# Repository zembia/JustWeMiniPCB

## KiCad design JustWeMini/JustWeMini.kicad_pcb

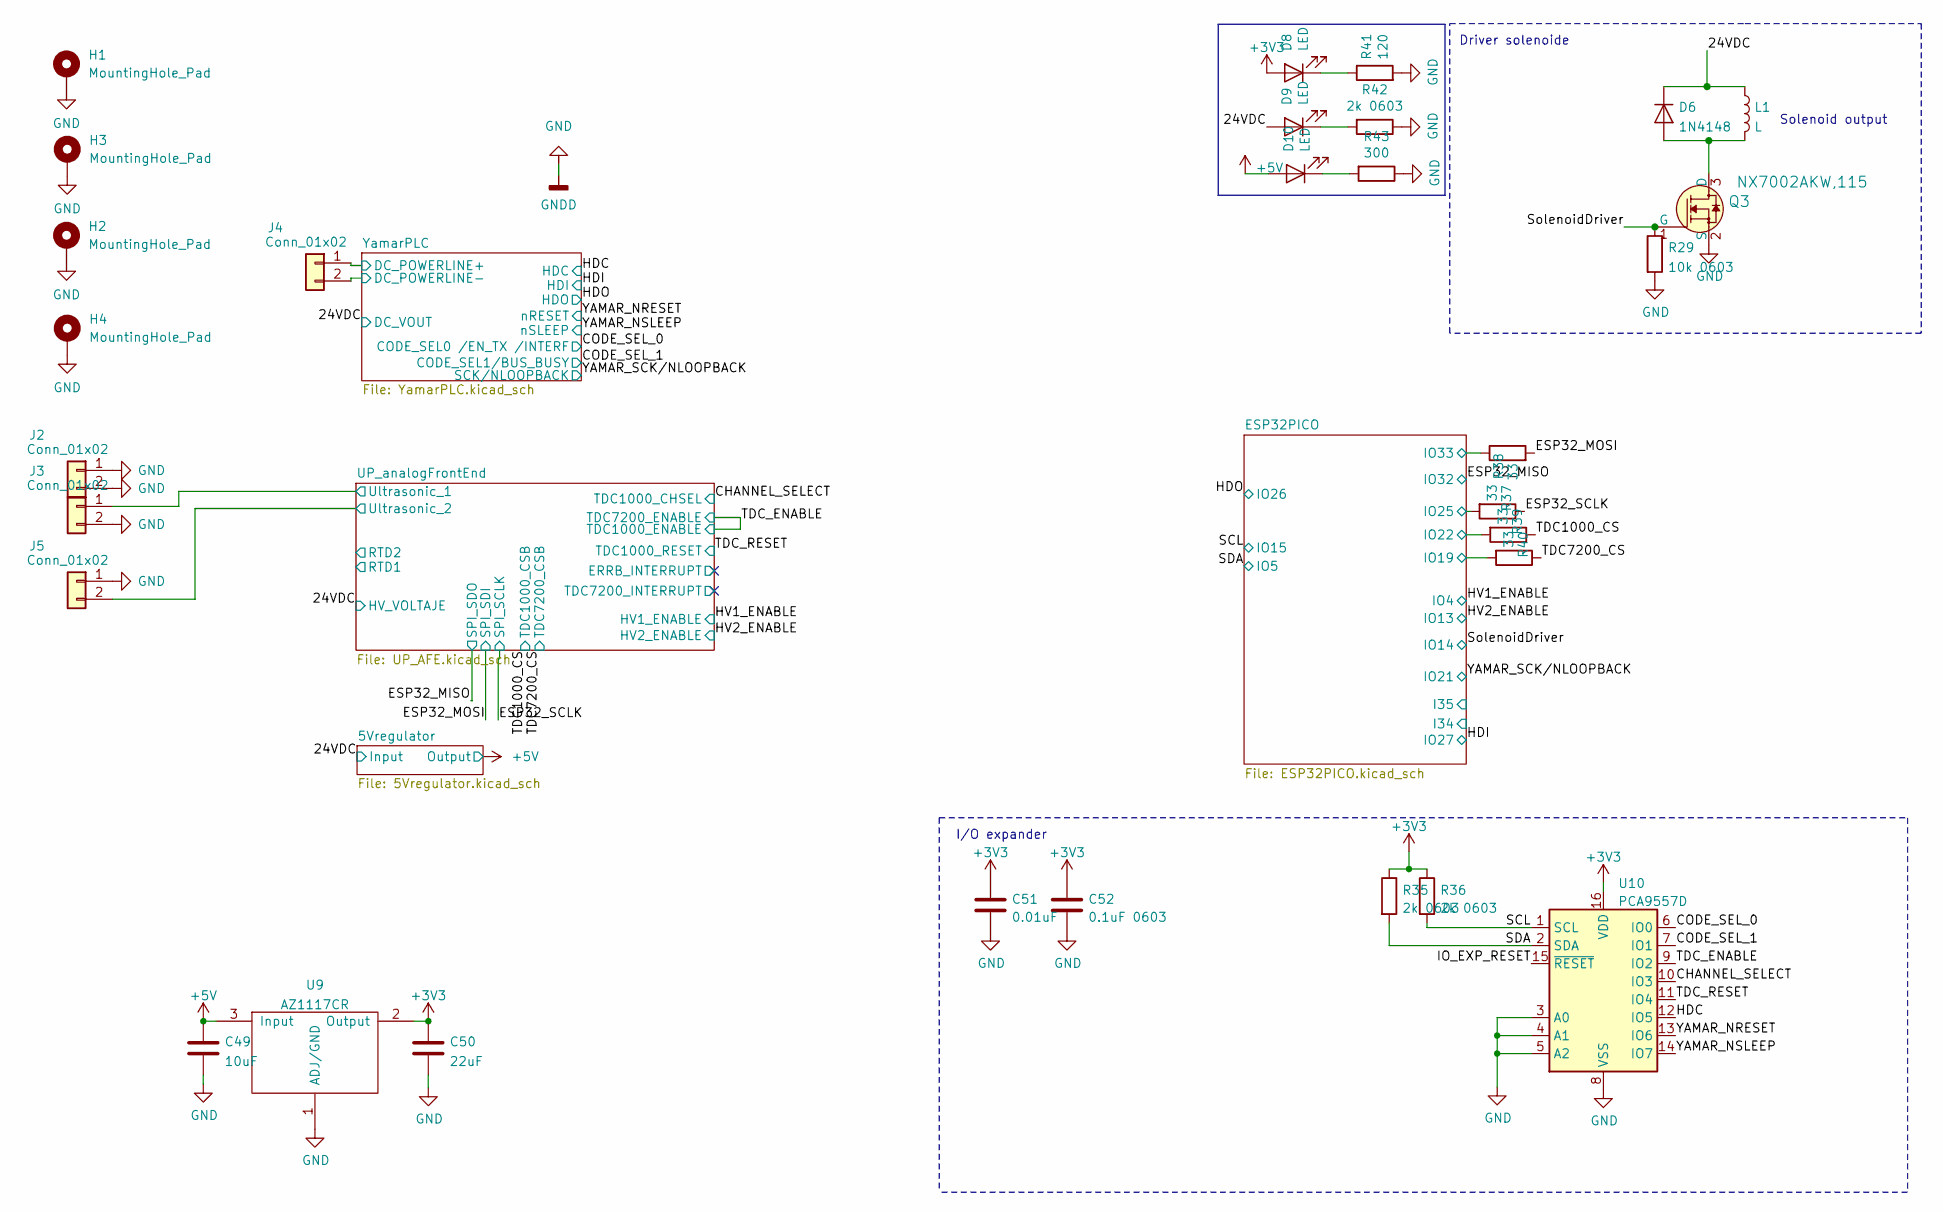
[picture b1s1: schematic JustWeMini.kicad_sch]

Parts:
C49: 10uF; C_0805_2012Metric; MPN GRM21BR6YA106ME43L
C50: 22uF; C_0603_1608Metric; MPN GRM187R61A226ME15D
C51: 0.01uF; C_0402_1005Metric; MPN CC0402JRX7R9BB103
C52: 0.1uF 0603; C_0603_1608Metric; MPN C0603C104K5RAC3121
D6: 1N4148; D_DO-35_SOD27_P7.62mm_Horizontal; MPN 1N4148
D8, D9, D10: LED; LED_0805_2012Metric; MPN SM0805UYC
H1, H2, H3, H4: MountingHole_Pad; MountingHole_3.2mm_M3_Pad_Via
J2, J3, J4, J5: Conn_01x02; CUI_TB007-508-02BE; MPN TB007-508-02BE
L1: L; CUI_TB007-508-02BE; MPN TB007-508-02BE
Q3: -; SOT-323_SC-70; MPN NX7002AKW,115
R29: 10k 0603; R_0603_1608Metric; MPN CR0603-FX-1002ELF
R35, R36, R42: 2k 0603; R_0603_1608Metric; MPN ERJ-PA3F2001V
R37, R38, R39, R40: 33; R_0402_1005Metric; MPN CR0402-FX-33R0GLF
R41: 120; R_0603_1608Metric; MPN CR0603-JW-121ELF
R43: 300; R_0603_1608Metric; MPN RC0603JR-07300RL
U9: AZ1117CR; SOT-89-3; MPN AZ1117CR-3.3TRG1
U10: PCA9557D; SO-16_3.9x9.9mm_P1.27mm; MPN PCA9557D

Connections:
+3V3: C50.1, C51.1, C52.1, D8.2 (A), R35.1, R36.1, U9.2 (Output), U10.16 (VDD); also elsewhere on the board
+5V: C49.1, D10.2 (A), U9.3 (Input); also elsewhere on the board
/24VDC: D6.1 (K), D9.2 (A), L1.1; also elsewhere on the board
/CHANNEL_SELECT: U10.10 (IO3); also elsewhere on the board
/CODE_SEL_0: U10.6 (IO0); also elsewhere on the board
/CODE_SEL_1: U10.7 (IO1); also elsewhere on the board
/ESP32PICO/IO19: R40.2; also elsewhere on the board
/ESP32PICO/IO22: R39.2; also elsewhere on the board
/ESP32PICO/IO25: R37.2; also elsewhere on the board
/ESP32PICO/IO33: R38.1; also elsewhere on the board
/ESP32_MOSI: R38.2; also elsewhere on the board
/ESP32_SCLK: R37.1; also elsewhere on the board
/HDC: U10.12 (IO5); also elsewhere on the board
/IO_EXP_RESET: U10.15 (~RESET)
/SCL: R36.2, U10.1 (SCL); also elsewhere on the board
/SDA: R35.2, U10.2 (SDA); also elsewhere on the board
/SolenoidDriver: Q3.1 (G), R29.1; also elsewhere on the board
/TDC1000_CS: R39.1; also elsewhere on the board
/TDC7200_CS: R40.1; also elsewhere on the board
/TDC_ENABLE: U10.9 (IO2); also elsewhere on the board
/TDC_RESET: U10.11 (IO4); also elsewhere on the board
/UP_analogFrontEnd/Ultrasonic_1: J3.1; also elsewhere on the board
/UP_analogFrontEnd/Ultrasonic_2: J5.2; also elsewhere on the board
/YAMAR_NRESET: U10.13 (IO6); also elsewhere on the board
/YAMAR_NSLEEP: U10.14 (IO7); also elsewhere on the board
/YamarPLC/DC_POWERLINE+: J4.1; also elsewhere on the board
GND: C49.2, C50.2, C51.2, C52.2, H1.1, H2.1, H3.1, H4.1, J2.1, J2.2, J3.2, J4.2, J5.1, Q3.2 (S), R29.2, R41.2, R42.1, R43.1, U9.1 (ADJ/GND), U10.3 (A0), U10.4 (A1), U10.5 (A2), U10.8 (VSS); also elsewhere on the board
unnamed: D6.2 (A), L1.2, Q3.3 (D)
unnamed: D8.1 (K), R41.1
unnamed: D9.1 (K), R42.2
unnamed: D10.1 (K), R43.2

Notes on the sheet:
Driver solenoide
Solenoid output
I/O expander

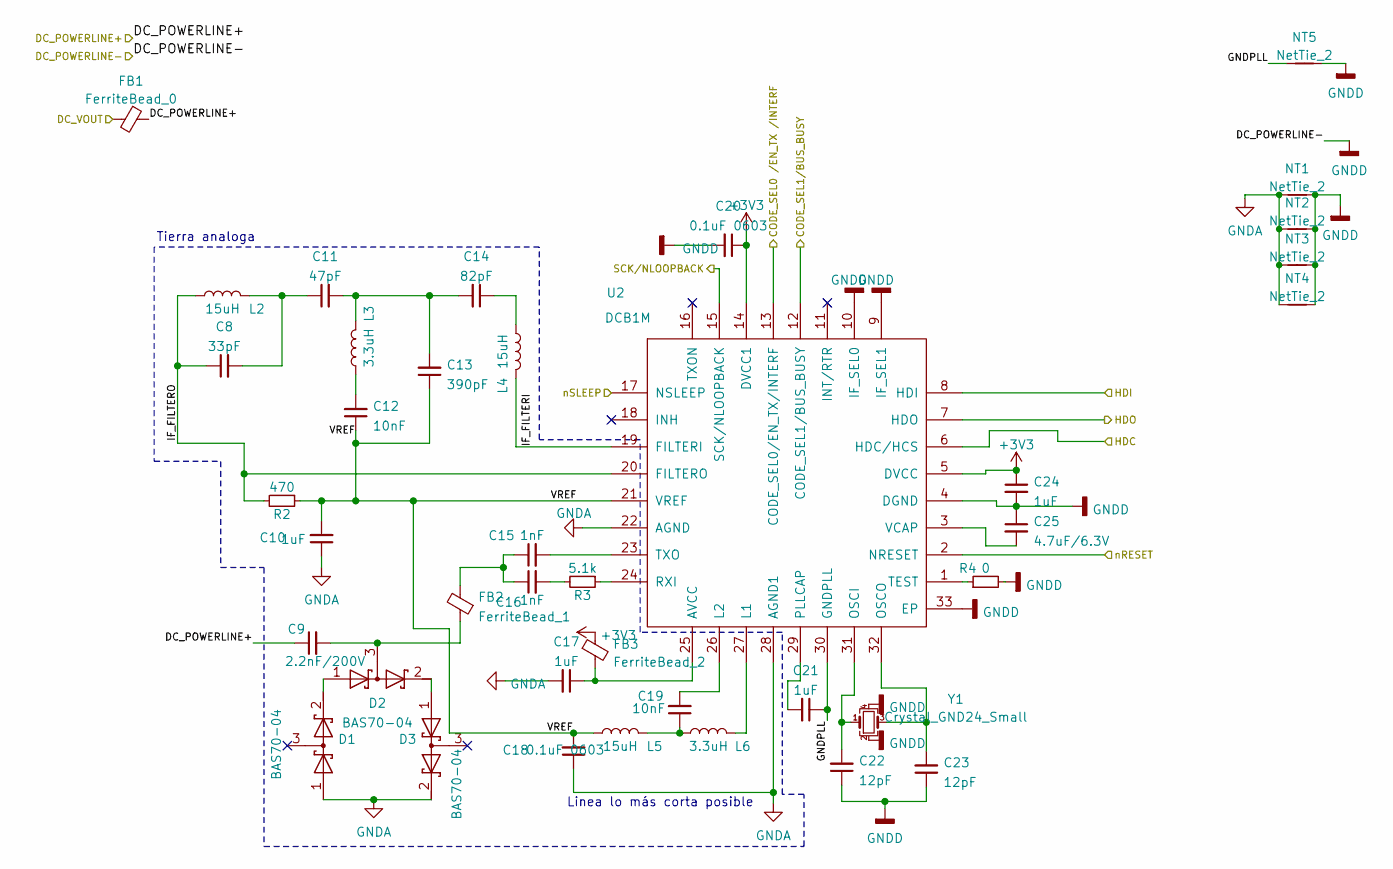
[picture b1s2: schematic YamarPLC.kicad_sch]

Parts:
C8: 33pF; C_0603_1608Metric; MPN 06035A330FAT2A
C9: 2.2nF/200V; C_0603_1608Metric; MPN C0603C222K2RECAUTO
C10, C17, C24: 1uF; C_0805_2012Metric; MPN C2012JB1V105M085AB
C11: 47pF; C_0402_1005Metric; MPN 0402N470J250CT
C12, C19: 10nF; C_0603_1608Metric; MPN VJ0603Y103KXAAC
C13: 390pF; C_0402_1005Metric; MPN 0402N391J250CT
C14: 82pF; C_0603_1608Metric; MPN VJ0603A820JXAAC
C15, C16: 1nF; C_0603_1608Metric; MPN GRM1885C1H102JA01D
C18, C20: 0.1uF 0603; C_0603_1608Metric; MPN C0603C104K5RAC3121
C21: 1uF; C_0603_1608Metric; MPN LMK107B7105KA-T
C22, C23: 12pF; C_0603_1608Metric; MPN VJ0603D120JXPAJ
C25: 4.7uF/6.3V; C_0603_1608Metric; MPN GCJ188C70J475KE02D
D1, D2, D3: BAS70-04; SOT-23; MPN BAS70-04 RFG
FB1: FerriteBead_0; L_Taiyo-Yuden_NR-50xx; MPN NRS5040T220MMGK
FB2: FerriteBead_1; L_0603_1608Metric; MPN-DK MI0603L301R-10
FB3: FerriteBead_2; L_0603_1608Metric; MPN HZ0603A222R-10
L2, L4, L5: 15uH; L_0805_2012Metric; MPN 815-AIML-0805-150K-T
L3, L6: 3.3uH; L_0805_2012Metric; MPN AIML-0805-3R3K-T
NT1, NT2, NT3, NT4, NT5: NetTie_2; NetTie-2_SMD_Pad0.25mm
R2: 470; R_0603_1608Metric; MPN CRGCQ0603F470R
R3: 5.1k; R_0603_1608Metric; MPN CR0603-JW-512ELF
R4: 0; R_0603_1608Metric; MPN CRCW06030000Z0EAHP
U2: DCB1M; QFN-32-1EP_5x5mm_P0.5mm_EP3.3x3.3mm; MPN DCB1M
Y1: Crystal_GND24_Small; Crystal_SMD_2016-4Pin_2.0x1.6mm; MPN ECS-160-12-37B-CTN-TR

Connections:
+3V3: C20.1, C24.1, FB3.1, U2.5 (DVCC), U2.14 (DVCC1); also elsewhere on the board
/24VDC: FB1.2; also elsewhere on the board
/CODE_SEL_0: U2.13 (CODE_SEL0/EN_TX/INTERF); also elsewhere on the board
/CODE_SEL_1: U2.12 (CODE_SEL1/BUS_BUSY); also elsewhere on the board
/HDC: U2.6 (HDC/HCS); also elsewhere on the board
/HDI: U2.8 (HDI); also elsewhere on the board
/HDO: U2.7 (HDO); also elsewhere on the board
/YAMAR_NRESET: U2.2 (NRESET); also elsewhere on the board
/YAMAR_NSLEEP: U2.17 (NSLEEP); also elsewhere on the board
/YAMAR_SCK/NLOOPBACK: U2.15 (SCK/NLOOPBACK); also elsewhere on the board
/YamarPLC/DC_POWERLINE+: C9.1, FB1.1; also elsewhere on the board
/YamarPLC/GNDPLL: C21.1, NT5.1, U2.30 (GNDPLL)
/YamarPLC/IF_FILTERI: L4.1, U2.19 (FILTERI)
/YamarPLC/IF_FILTERO: C8.1, L2.2, R2.2, U2.20 (FILTERO)
/YamarPLC/VREF: C10.2, C12.1, C13.1, C18.2, L5.2, R2.1, U2.21 (VREF)
GND: C20.2, C22.1, C23.1, C24.2, C25.1, NT1.2, NT2.2, NT3.2, NT4.2, NT5.2, R4.2, U2.4 (DGND), U2.9 (IF_SEL1), U2.10 (IF_SEL0), U2.33 (EP), Y1.2, Y1.4; also elsewhere on the board
GNDA: C10.1, C17.2, C18.1, D1.1 (A), D3.2 (K), NT1.1, NT2.1, NT3.1, NT4.1, U2.22 (AGND), U2.28 (AGND1)
unnamed: C9.2, D2.3 (common), FB2.1
unnamed: C8.2, C11.1, L2.1
unnamed: C11.2, C13.2, C14.2, L3.1
unnamed: C12.2, L3.2
unnamed: C14.1, L4.2
unnamed: C15.1, C16.1, FB2.2
unnamed: C15.2, U2.23 (TXO)
unnamed: C16.2, R3.2
unnamed: C17.1, FB3.2, U2.25 (AVCC)
unnamed: C19.1, L5.1, L6.2
unnamed: C19.2, U2.26 (L2)
unnamed: C21.2, U2.29 (PLLCAP)
unnamed: C22.2, U2.31 (OSCI), Y1.1
unnamed: C23.2, U2.32 (OSCO), Y1.3
unnamed: C25.2, U2.3 (VCAP)
unnamed: D1.2 (K), D2.1 (A)
unnamed: D2.2 (K), D3.1 (A)
unnamed: L6.1, U2.27 (L1)
unnamed: R3.1, U2.24 (RXI)
unnamed: R4.1, U2.1 (TEST)

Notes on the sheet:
Linea lo más corta posible
Tierra analoga

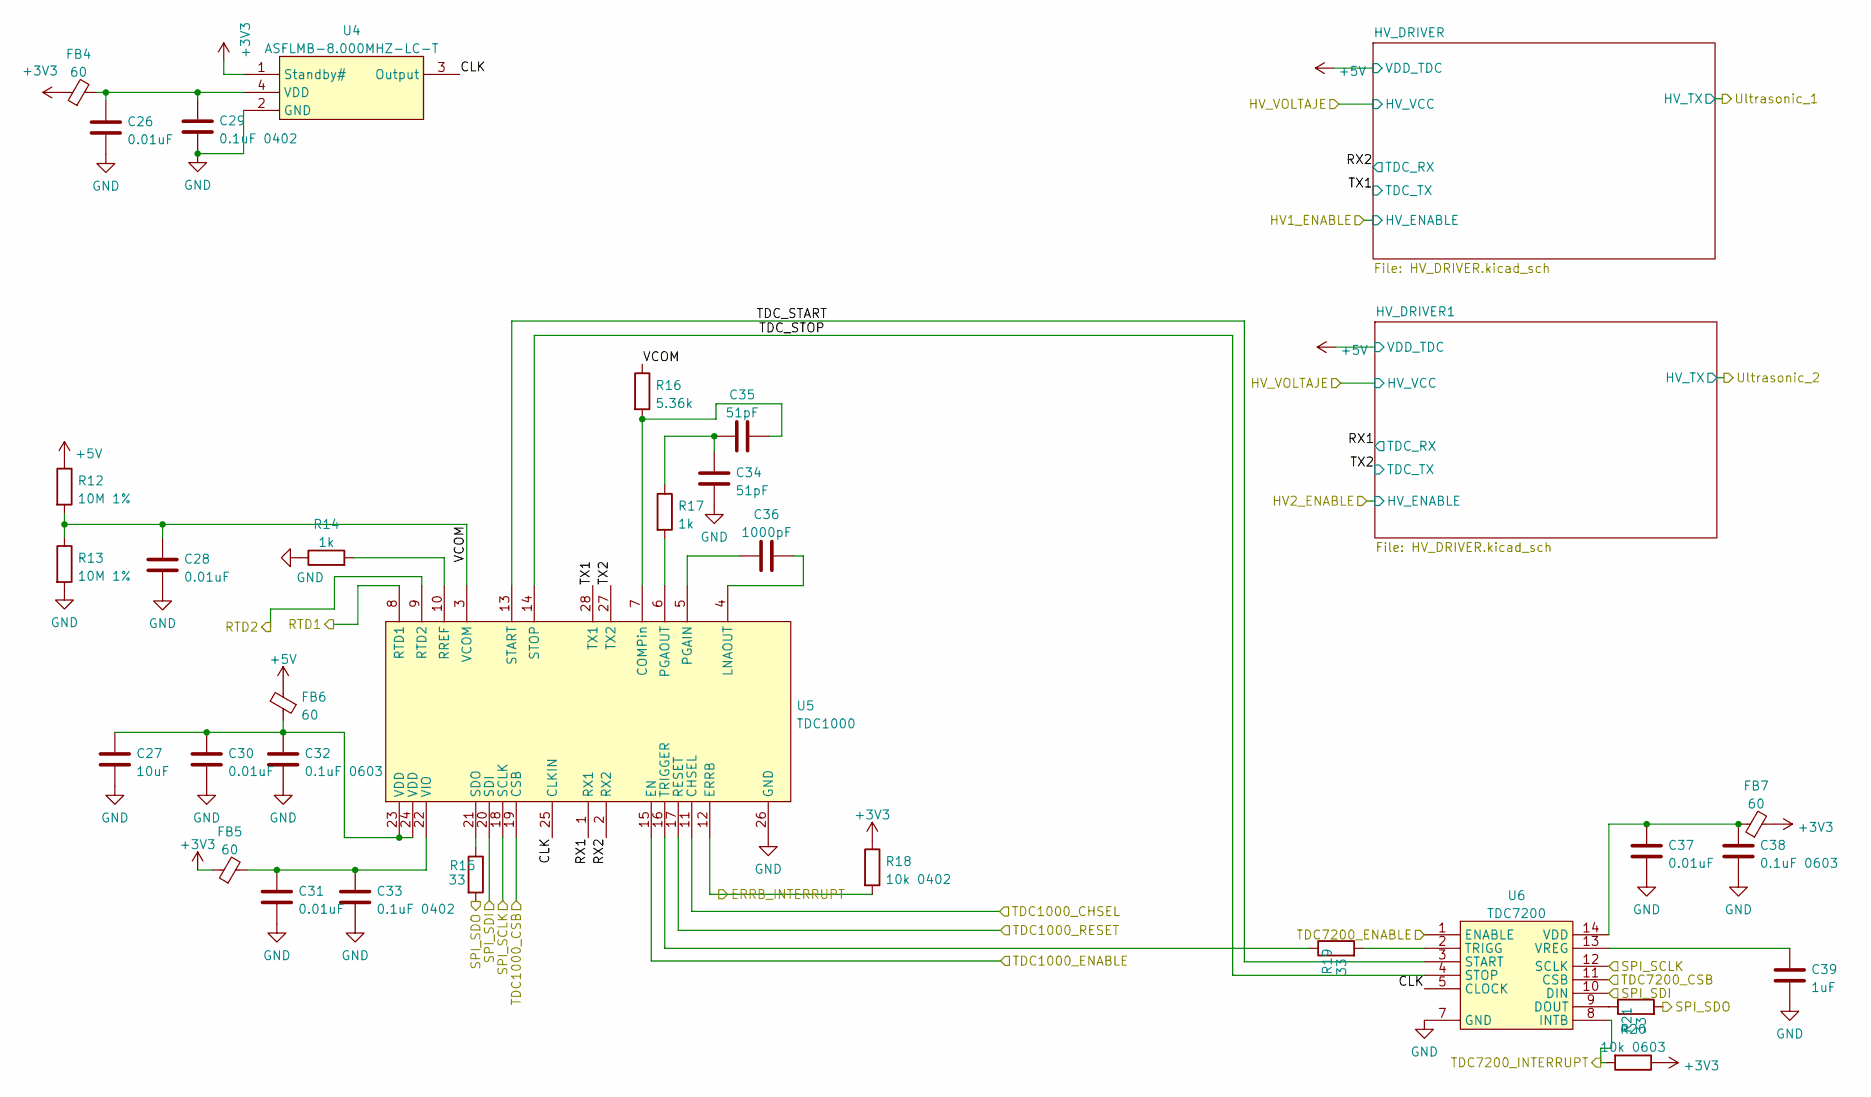
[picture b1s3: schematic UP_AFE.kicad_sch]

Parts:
C26, C28, C30, C31, C37: 0.01uF; C_0402_1005Metric; MPN CC0402JRX7R9BB103
C27: 10uF; C_0805_2012Metric; MPN GRM21BR6YA106ME43L
C29, C33: 0.1uF 0402; C_0402_1005Metric; MPN CL05F104ZO5NNND
C32, C38: 0.1uF 0603; C_0603_1608Metric; MPN C0603C104K5RAC3121
C34, C35: 51pF; C_0402_1005Metric; MPN CC0402JRNPO9BN510
C36: 1000pF; C_0402_1005Metric; MPN 0402B102J500CT
C39: 1uF; C_0805_2012Metric; MPN C2012JB1V105M085AB
FB4, FB5, FB6, FB7: 60; L_0402_1005Metric; MPN ACML-0402HC-600-T
R12, R13: 10M 1%; R_0402_1005Metric; MPN RC0402FR-0710ML
R14, R17: 1k; R_0402_1005Metric; MPN RC0402JR-071KL
R15, R19, R21: 33; R_0402_1005Metric; MPN CR0402-FX-33R0GLF
R16: 5.36k; R_0603_1608Metric; MPN AC0603FR-075K36L
R18: 10k 0402; R_0402_1005Metric; MPN WR04X1002FTL
R20: 10k 0603; R_0603_1608Metric; MPN CR0603-FX-1002ELF
U4: ASFLMB-8.000MHZ-LC-T; ASFLMB; MPN ASFLMB-8.000MHZ-LC-T
U5: TDC1000; TSSOP-28_4.4x9.7mm_P0.65mm; MPN TDC1000PW
U6: TDC7200; TSSOP-14_4.4x5mm_P0.65mm; MPN TDC7200PWR

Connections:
+3V3: FB4.1, FB5.1, FB7.2, R18.1, R20.1, U4.1 (Standby#); also elsewhere on the board
+5V: FB6.2, R12.1; also elsewhere on the board
/CHANNEL_SELECT: U5.11 (CHSEL); also elsewhere on the board
/ESP32_MISO: R15.2, R21.2; also elsewhere on the board
/ESP32_MOSI: U5.20 (SDI), U6.10 (DIN); also elsewhere on the board
/ESP32_SCLK: U5.18 (SCLK), U6.12 (SCLK); also elsewhere on the board
/TDC1000_CS: U5.19 (CSB); also elsewhere on the board
/TDC7200_CS: U6.11 (CSB); also elsewhere on the board
/TDC_ENABLE: U5.15 (EN), U6.1 (ENABLE); also elsewhere on the board
/TDC_RESET: U5.17 (RESET); also elsewhere on the board
/UP_analogFrontEnd/CLK: U4.3 (Output), U5.25 (CLKIN), U6.5 (CLOCK)
/UP_analogFrontEnd/ERRB_INTERRUPT: R18.2, U5.12 (ERRB)
/UP_analogFrontEnd/RTD1: U5.8 (RTD1)
/UP_analogFrontEnd/RTD2: U5.9 (RTD2)
/UP_analogFrontEnd/RX1: U5.1 (RX1); also elsewhere on the board
/UP_analogFrontEnd/RX2: U5.2 (RX2); also elsewhere on the board
/UP_analogFrontEnd/TDC7200_INTERRUPT: R20.2, U6.8 (INTB)
/UP_analogFrontEnd/TDC_START: U5.13 (START), U6.3 (START)
/UP_analogFrontEnd/TDC_STOP: U5.14 (STOP), U6.4 (STOP)
/UP_analogFrontEnd/TX1: U5.28 (TX1); also elsewhere on the board
/UP_analogFrontEnd/TX2: U5.27 (TX2); also elsewhere on the board
/UP_analogFrontEnd/VCOM: C28.1, R12.2, R13.1, R16.1, U5.3 (VCOM)
GND: C26.2, C27.2, C28.2, C29.2, C30.2, C31.2, C32.2, C33.2, C34.1, C37.2, C38.2, C39.2, R13.2, R14.1, U4.2 (GND), U5.26 (GND), U6.7 (GND); also elsewhere on the board
unnamed: C26.1, C29.1, FB4.2, U4.4 (VDD)
unnamed: C27.1, C30.1, C32.1, FB6.1, U5.23 (VDD), U5.24 (VDD)
unnamed: C31.1, C33.1, FB5.2, U5.22 (VIO)
unnamed: C34.2, C35.1, R17.1
unnamed: C35.2, R16.2, U5.7 (COMPin)
unnamed: C36.1, U5.5 (PGAIN)
unnamed: C36.2, U5.4 (LNAOUT)
unnamed: C37.1, C38.1, FB7.1, U6.14 (VDD)
unnamed: C39.1, U6.13 (VREG)
unnamed: R14.2, U5.10 (RREF)
unnamed: R15.1, U5.21 (SDO)
unnamed: R17.2, U5.6 (PGAOUT)
unnamed: R19.1, U5.16 (TRIGGER)
unnamed: R19.2, U6.2 (TRIGG)
unnamed: R21.1, U6.9 (DOUT)

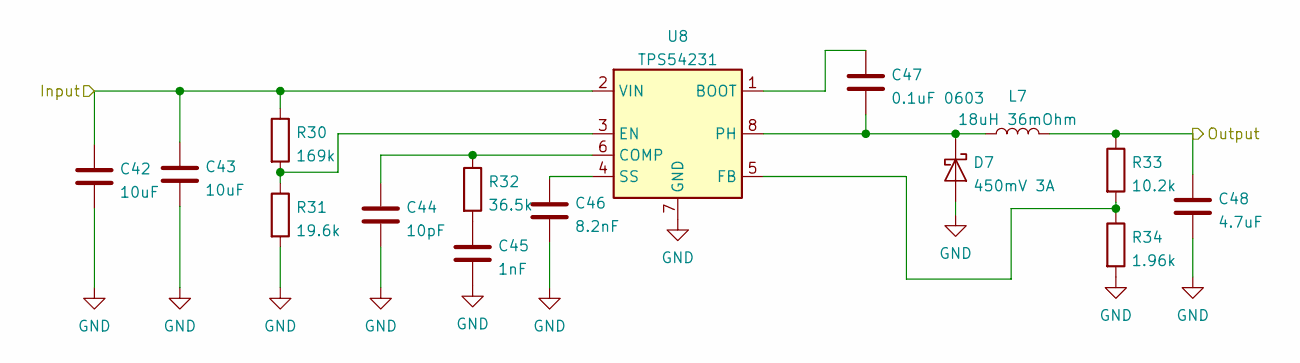
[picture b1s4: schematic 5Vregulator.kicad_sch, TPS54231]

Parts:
C42, C43: 10uF; C_0805_2012Metric; MPN GRM21BR6YA106ME43L
C44: 10pF; C_0603_1608Metric; MPN 06035C100KAT2A
C45: 1nF; C_0603_1608Metric; MPN GRM1885C1H102JA01D
C46: 8.2nF; C_0603_1608Metric; MPN CGA3E2C0G1H822J080AE
C47: 0.1uF 0603; C_0603_1608Metric; MPN C0603C104K5RAC3121
C48: 4.7uF; C_0603_1608Metric; MPN C1608JB1E475M080AC
D7: 450mV 3A; D_SMA; MPN B340A-E3/61T
L7: 18uH 36mOhm; L_Bourns_SRR1260; MPN SRR1280-180M
R30: 169k; R_0603_1608Metric; MPN RC0603FR-07169KL
R31: 19.6k; R_0603_1608Metric; MPN RC0603FR-0719K6L
R32: 36.5k; R_0603_1608Metric; MPN CR0603-FX-3652ELF
R33: 10.2k; R_0603_1608Metric; MPN RC0603FR-1310K2L
R34: 1.96k; R_0603_1608Metric; MPN AC0603FR-071K96L
U8: TPS54231; SOIC-8_3.9x4.9mm_P1.27mm; MPN TPS54231DR

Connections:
+5V: C48.1, L7.2, R33.1; also elsewhere on the board
/24VDC: C42.1, C43.1, R30.1, U8.2 (VIN); also elsewhere on the board
GND: C42.2, C43.2, C44.2, C45.2, C46.2, C48.2, D7.2 (A), R31.2, R34.2, U8.7 (GND); also elsewhere on the board
unnamed: C44.1, R32.1, U8.6 (COMP)
unnamed: C45.1, R32.2
unnamed: C46.1, U8.4 (SS)
unnamed: C47.1, U8.1 (BOOT)
unnamed: C47.2, D7.1 (K), L7.1, U8.8 (PH)
unnamed: R30.2, R31.1, U8.3 (EN)
unnamed: R33.2, R34.1, U8.5 (FB)

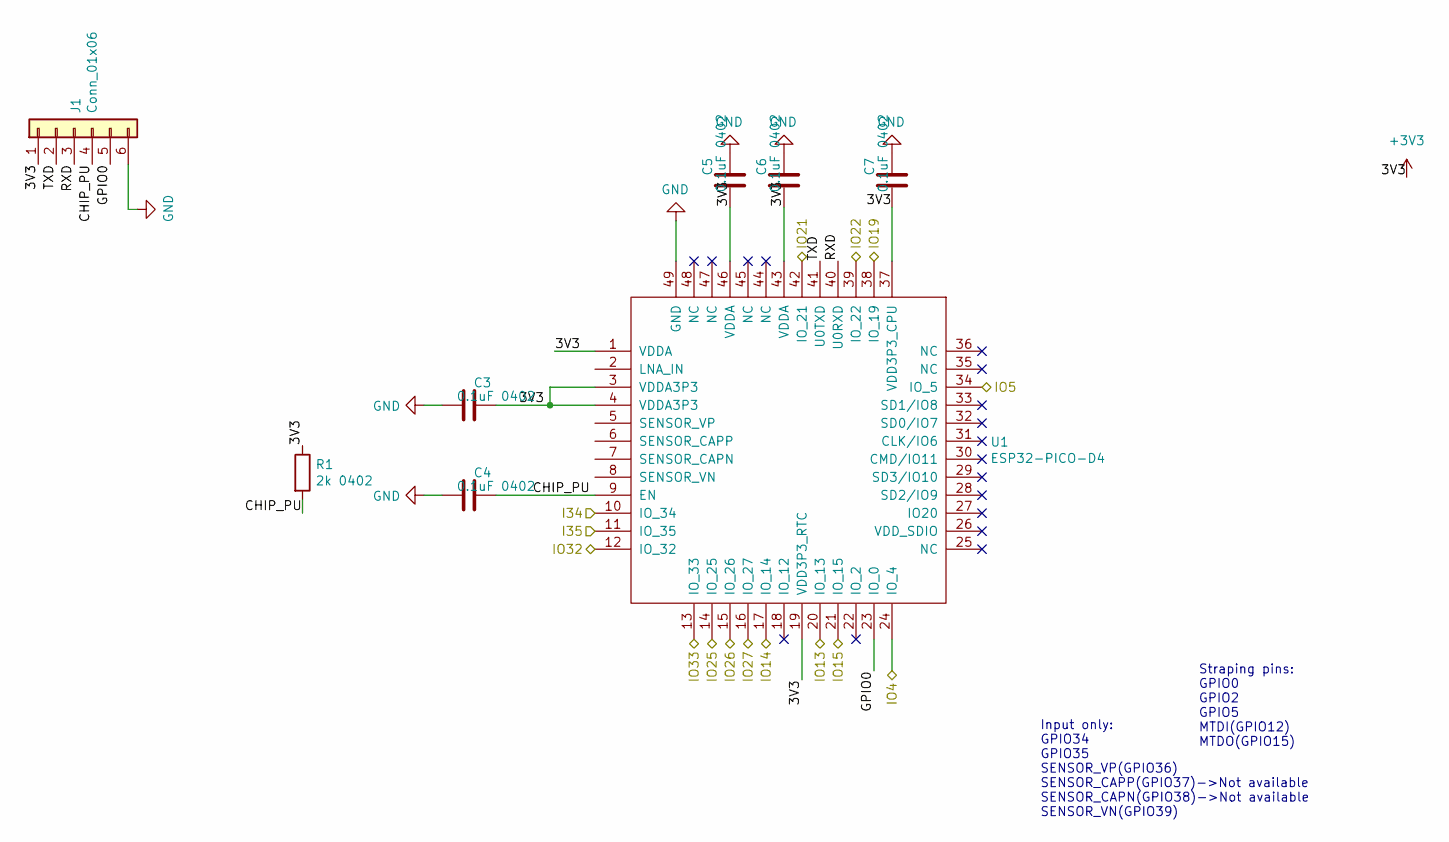
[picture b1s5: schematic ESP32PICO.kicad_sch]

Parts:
C3, C4, C5, C6, C7: 0.1uF 0402; C_0402_1005Metric; MPN CL05F104ZO5NNND
J1: Conn_01x06; JST_PH_B6B-PH-K_1x06_P2.00mm_Vertical; MPN 440054-6
R1: 2k 0402; R_0402_1005Metric; MPN CR0402-JW-202GLF
U1: ESP32-PICO-D4; ESP32-PICO-D4-QFN48; MPN ESP32-PICO-D4

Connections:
+3V3: C3.2, C5.1, C6.1, C7.1, J1.1, R1.1, U1.1 (VDDA), U1.3 (VDDA3P3), U1.4 (VDDA3P3), U1.19 (VDD3P3_RTC), U1.37 (VDD3P3_CPU), U1.43 (VDDA), U1.46 (VDDA); also elsewhere on the board
/ESP32PICO/CHIP_PU: C4.2, J1.4, R1.2, U1.9 (EN)
/ESP32PICO/GPIO0: J1.5, U1.23 (IO_0)
/ESP32PICO/I34: U1.10 (IO_34)
/ESP32PICO/I35: U1.11 (IO_35)
/ESP32PICO/IO19: U1.38 (IO_19); also elsewhere on the board
/ESP32PICO/IO22: U1.39 (IO_22); also elsewhere on the board
/ESP32PICO/IO25: U1.14 (IO_25); also elsewhere on the board
/ESP32PICO/IO33: U1.13 (IO_33); also elsewhere on the board
/ESP32PICO/RXD: J1.3, U1.40 (U0RXD)
/ESP32PICO/TXD: J1.2, U1.41 (U0TXD)
/ESP32_MISO: U1.12 (IO_32); also elsewhere on the board
/HDI: U1.16 (IO_27); also elsewhere on the board
/HDO: U1.15 (IO_26); also elsewhere on the board
/HV1_ENABLE: U1.24 (IO_4); also elsewhere on the board
/HV2_ENABLE: U1.20 (IO_13); also elsewhere on the board
/SCL: U1.21 (IO_15); also elsewhere on the board
/SDA: U1.34 (IO_5); also elsewhere on the board
/SolenoidDriver: U1.17 (IO_14); also elsewhere on the board
/YAMAR_SCK/NLOOPBACK: U1.42 (IO_21); also elsewhere on the board
GND: C3.1, C4.1, C5.2, C6.2, C7.2, J1.6, U1.49 (GND); also elsewhere on the board

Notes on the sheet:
Straping pins: GPIO0 GPIO2 GPIO5 MTDI(GPIO12) MTDO(GPIO15)
Input only: GPIO34 GPIO35 SENSOR_VP(GPIO36) SENSOR_CAPP(GPIO37)->Not available SENSOR_CAPN(GPIO38)->Not available SENSOR_VN(GPIO39)

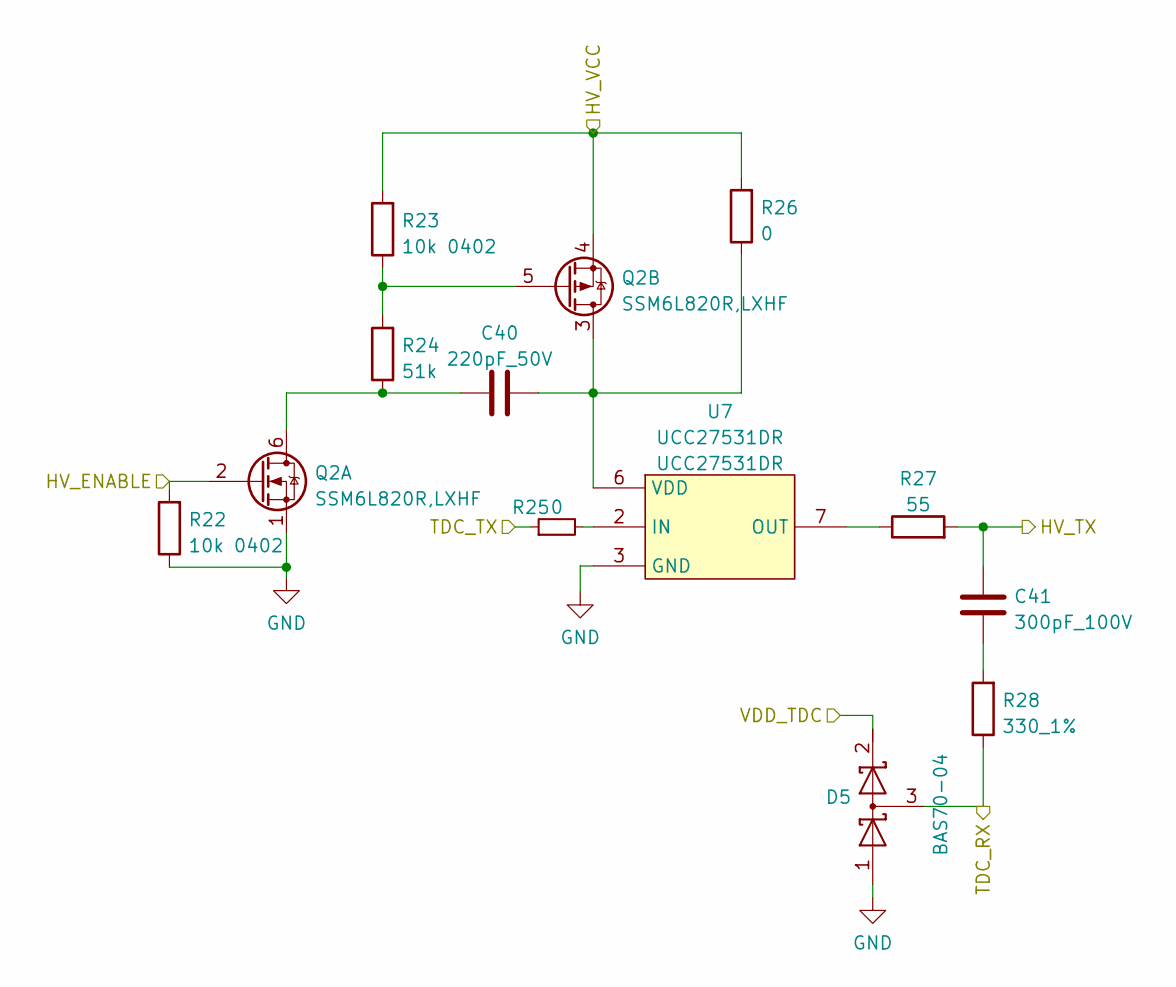
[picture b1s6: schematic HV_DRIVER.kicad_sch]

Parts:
C40: 220pF_50V; R_0402_1005Metric; MPN C0402C221J5GACTU
C41: 300pF_100V; C_0603_1608Metric; MPN GCM1885C2A301JA16D
D5: BAS70-04; SOT-23; MPN BAS70-04 RFG
Q2: SSM6L820R; TSOP-6_1.65x3.05mm_P0.95mm; MPN SSM6L820R,LXHF
R22, R23: 10k 0402; R_0402_1005Metric; MPN WR04X1002FTL
R24: 51k; R_0402_1005Metric; MPN RC0402JR-0751KL
R25: 0; R_0603_1608Metric; MPN CRCW06030000Z0EAHP
R26: 0; R_0402_1005Metric
R27: 55; R_0402_1005Metric; MPN RC0402FR-0754R9L
R28: 330_1%; R_0603_1608Metric; MPN RC0603FR-07330RL
U7: UCC27531DR; SOIC-8_3.9x4.9mm_P1.27mm; MPN UCC27531DR

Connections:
+5V: D5.2 (K); also elsewhere on the board
/24VDC: Q2.4 (1), R23.2, R26.2; also elsewhere on the board
/HV1_ENABLE: Q2.2 (G), R22.2; also elsewhere on the board
/UP_analogFrontEnd/RX2: D5.3 (common), R28.1; also elsewhere on the board
/UP_analogFrontEnd/TX1: R25.1; also elsewhere on the board
/UP_analogFrontEnd/Ultrasonic_1: C41.1, R27.2; also elsewhere on the board
GND: D5.1 (A), Q2.1 (S), R22.1, U7.3 (GND); also elsewhere on the board
unnamed: C40.1, Q2.6 (D), R24.1
unnamed: C40.2, Q2.3 (D), R26.1, U7.6 (VDD)
unnamed: C41.2, R28.2
unnamed: Q2.5 (G), R23.1, R24.2
unnamed: R25.2, U7.2 (IN)
unnamed: R27.1, U7.7 (OUT)

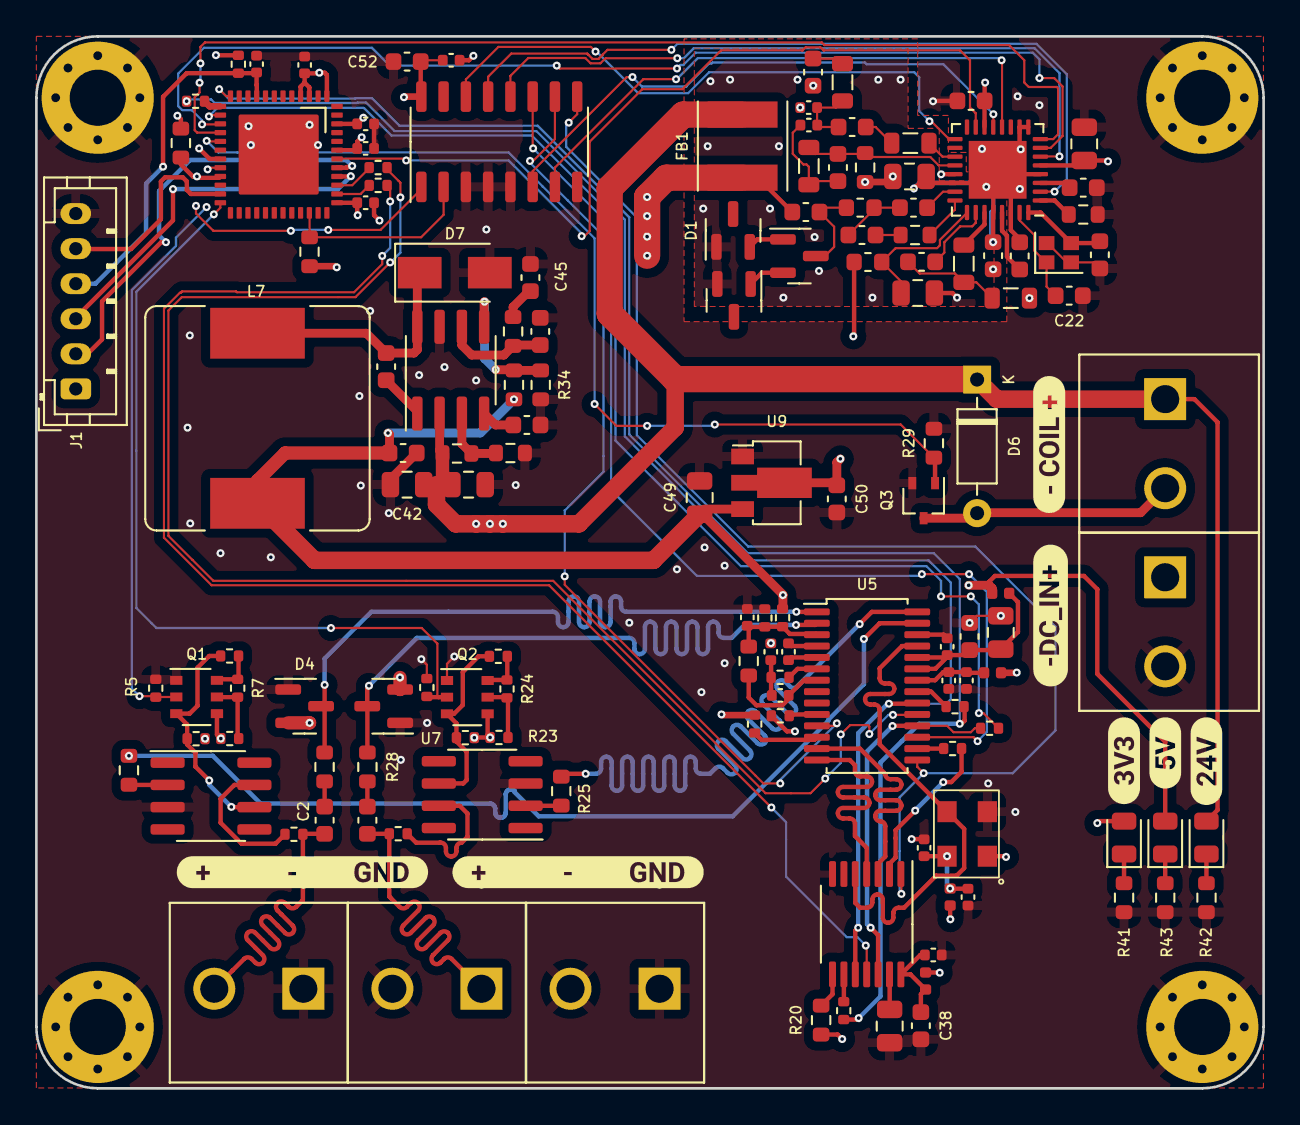
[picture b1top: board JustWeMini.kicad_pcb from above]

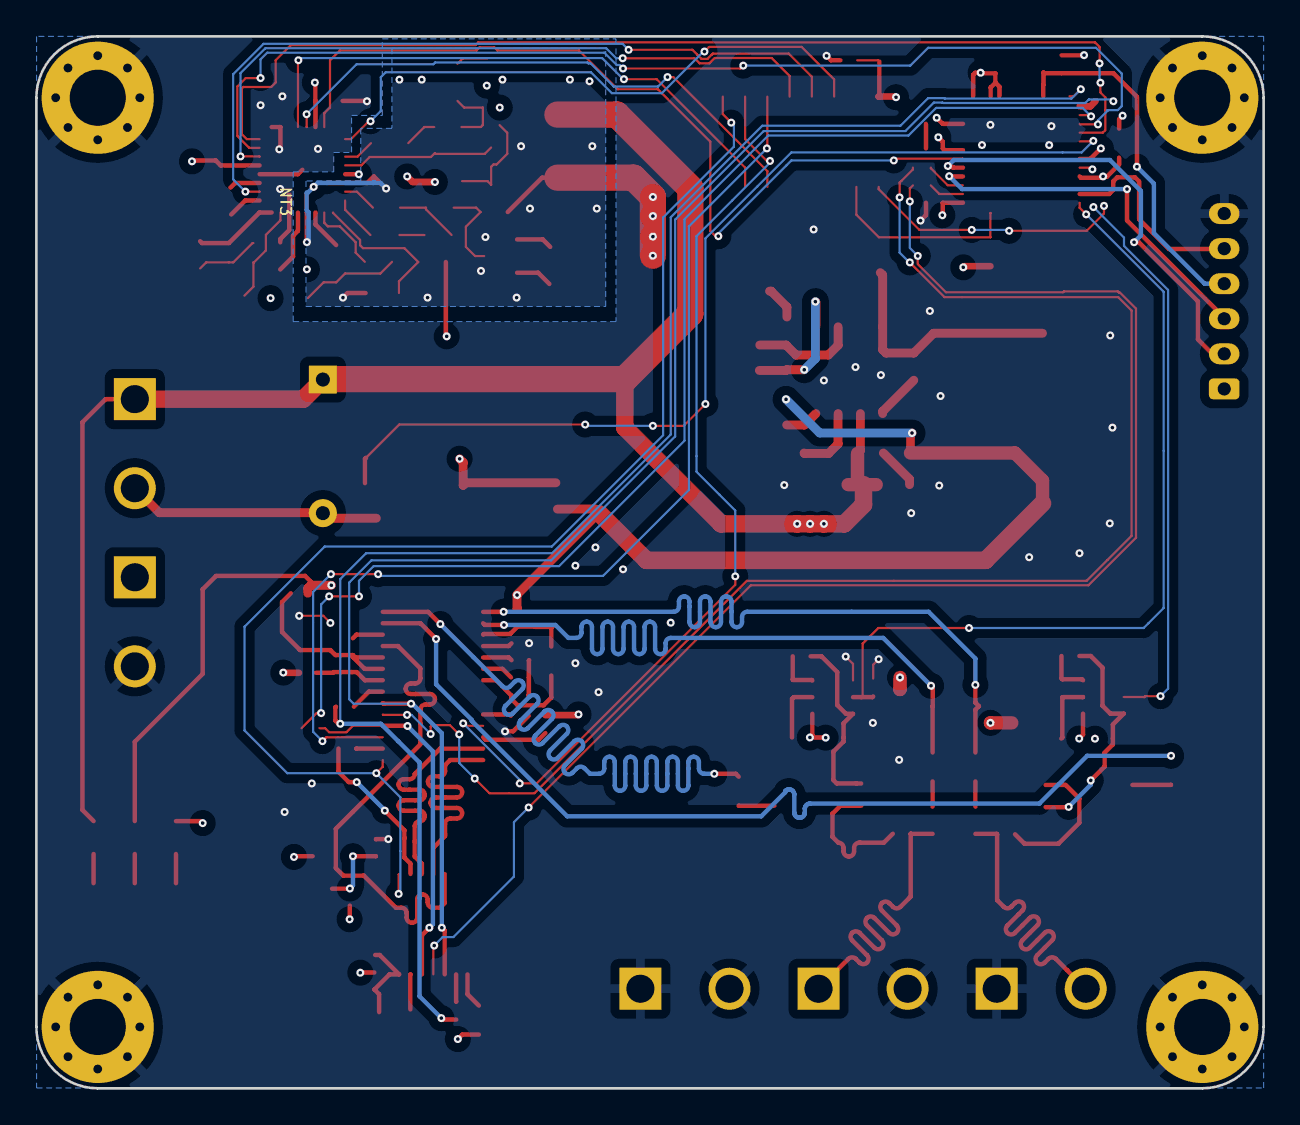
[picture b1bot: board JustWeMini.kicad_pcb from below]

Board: 4 copper layers, 70.0 x 60.0 mm, 154 parts (2 on the bottom side), 109 nets.

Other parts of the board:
C1: 220pF_50V; R_0402_1005Metric
C2: 300pF_100V; C_0603_1608Metric
D4: BAS70-04; SOT-23
Q1: SSM6L820R; TSOP-6_1.65x3.05mm_P0.95mm
R5, R6: 10k; R_0402_1005Metric
R7: 51k; R_0402_1005Metric
R8: 0; R_0603_1608Metric
R9: 0; R_0402_1005Metric
R10: 55; R_0402_1005Metric
R11: 330_1%; R_0603_1608Metric
U3: UCC27531DR; SOIC-8_3.9x4.9mm_P1.27mm
kibuzzard-63F8DB2A: G***; kibuzzard-63F8DB2A
kibuzzard-63F8DB3C: G***; kibuzzard-63F8DB3C
kibuzzard-63F90A85, kibuzzard-63F90A85#2: G***; kibuzzard-63F90A85
kibuzzard-63FCB37D: G***; kibuzzard-63FCB37D
kibuzzard-63FCB359: G***; kibuzzard-63FCB359
kibuzzard-63FCB372: G***; kibuzzard-63FCB372

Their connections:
+5V: D4.2 (K); also elsewhere on the board
/24VDC: Q1.4 (1), R6.2, R9.2; also elsewhere on the board
/HV2_ENABLE: Q1.2 (G), R5.2; also elsewhere on the board
/UP_analogFrontEnd/RX1: D4.3 (common), R11.1; also elsewhere on the board
/UP_analogFrontEnd/TX2: R8.1; also elsewhere on the board
/UP_analogFrontEnd/Ultrasonic_2: C2.1, R10.2; also elsewhere on the board
GND: D4.1 (A), Q1.1 (S), R5.1, U3.3 (GND); also elsewhere on the board
unnamed: C1.1, Q1.6 (D), R7.1
unnamed: C1.2, Q1.3 (D), R9.1, U3.6 (VDD)
unnamed: C2.2, R11.2
unnamed: Q1.5 (G), R6.1, R7.2
unnamed: R8.2, U3.2 (IN)
unnamed: R10.1, U3.7 (OUT)

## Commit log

2023-02-27 Feat: minimal changes, added LED, fixed serigraphy
2023-02-28 Feat: MPN adjusted
2023-02-28 feat: Adjust silkscreen and board edgecut
